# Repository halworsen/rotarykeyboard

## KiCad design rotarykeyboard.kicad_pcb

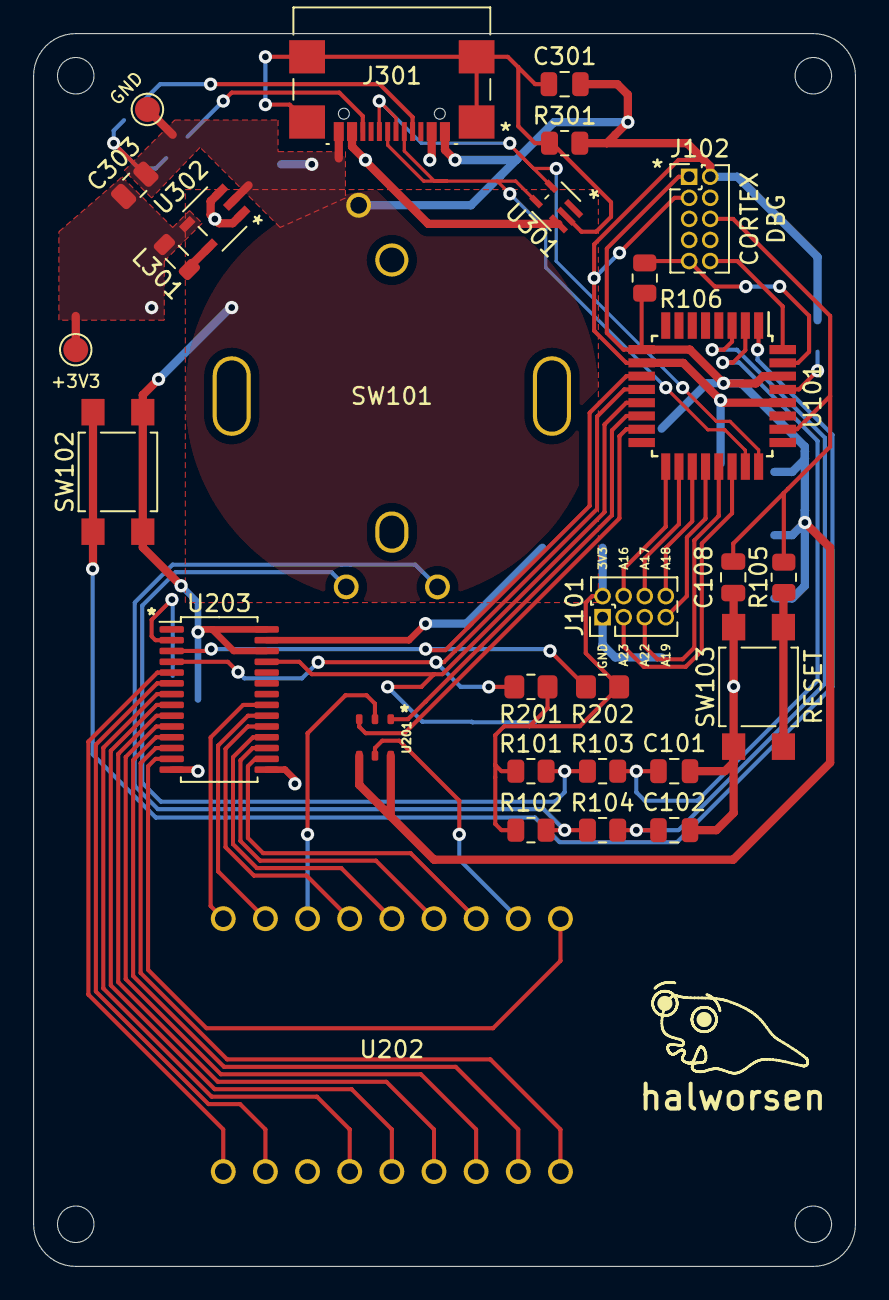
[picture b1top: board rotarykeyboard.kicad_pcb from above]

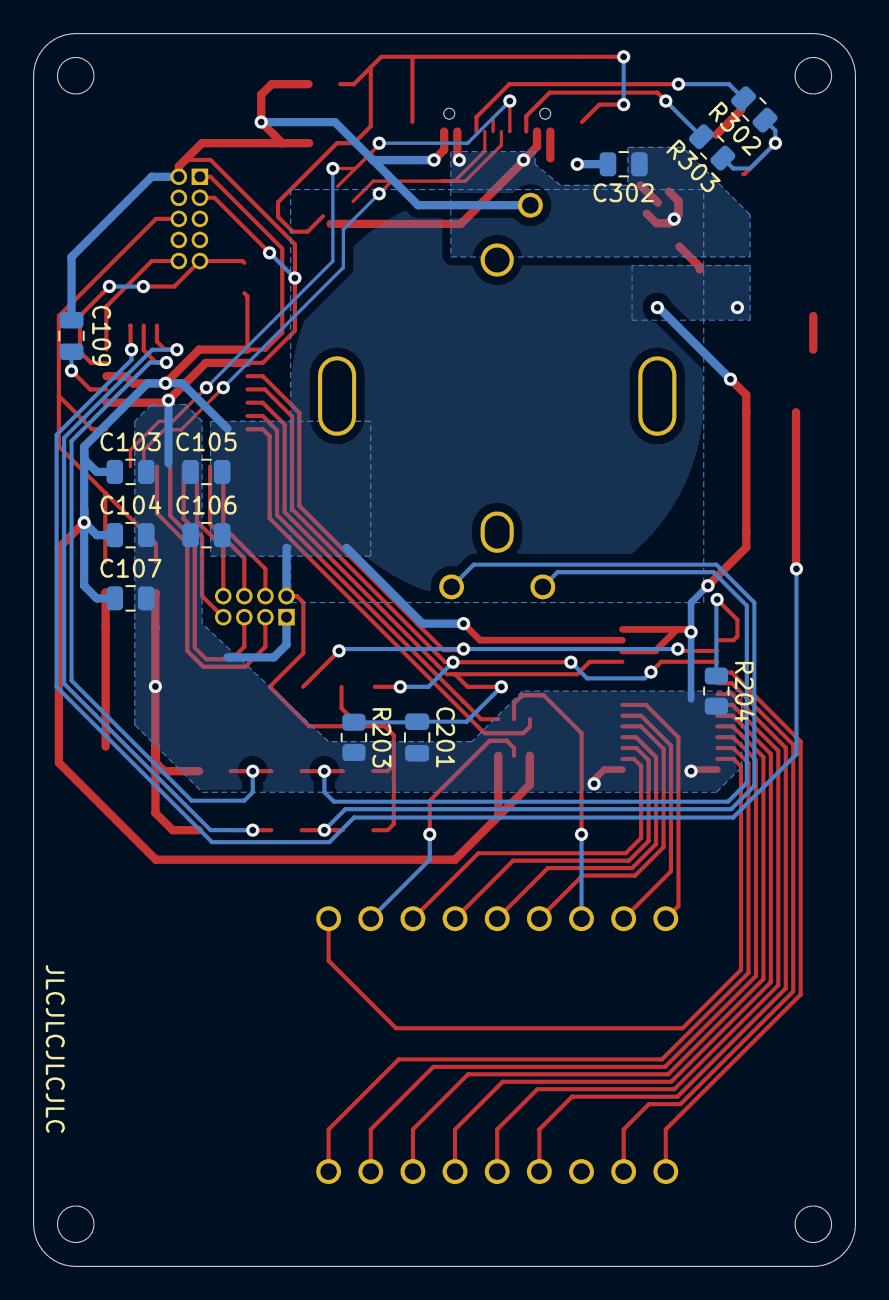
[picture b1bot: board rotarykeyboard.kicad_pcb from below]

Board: 2 copper layers, 49.5 x 74.3 mm, 41 parts (12 on the bottom side), 48 nets.

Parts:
+3V3: TestPoint; TestPoint_Pad_D1.5mm
C101, C102: 10n; C_0805_2012Metric
C103, C104, C105, C108, C201: 0.1u; C_0805_2012Metric
C106, C107, C302: 10u; C_0805_2012Metric
C109: 1u; C_0805_2012Metric
C301: 5n; C_0805_2012Metric
C303: 22u; C_0805_2012Metric
GND: TestPoint; TestPoint_Pad_D1.5mm
J101: Breakout; PinHeader_2x04_P1.27mm_Vertical
J102: Cortex Debug; PinHeader_2x05_P1.27mm_Vertical
J301: USB_C_Receptacle_USB2.0; USB4110-GF-A
L301: 10u; L_0805_2012Metric
R101, R102, R103, R104, R302, R303: 10K; R_0805_2012Metric
R105: 330; R_0805_2012Metric
R106: 1k; R_0805_2012Metric
R201, R202: 4k7; R_0805_2012Metric_Pad1.20x1.40mm_HandSolder
R203: 100k; R_0805_2012Metric
R204: 10k; R_0805_2012Metric
R301: 1M; R_0805_2012Metric
SW101: RotaryEncoder; EVQV6
SW102: KBPush; SW_SPST_TL3305A
SW103: RESET; SW_SPST_TL3305A
U101: ATSAMDA1E14B-ABT; TQFP-32_7x7mm_P0.8mm
U201: QS6K1FRATR; QS6K1FRA
U202: HDSP-A22C; LTP-3784E
U203: IS32FL3238; TSSOP-28_4.4x9.7mm_P0.65mm
U301: BZA856AVL
U302: XC9265A331MR-G

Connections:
+3V3: +3V3.1, C103.1, C104.1, C105.1, C106.1, C107.1, C303.1, J101.2, J102.1, L301.2, R101.1, R102.1, R106.2, R201.1, R202.1, U101.9 (VDDANA), U101.30 (VDDIN), U201.4 (D2), U201.6 (D1), U203.27 (VCC), U302.4 (VOUT)
+5V: C302.1, J301.A4 (VBUS), J301.A9 (VBUS), U301.3 (F), U302.1 (VIN), U302.3 (CE)
/Segment display/C1: U101.14 (PA11), U201.1 (G1)
/Segment display/C2: U101.15 (PA14), U201.3 (G2)
/Segment display/EN: C201.1, R203.1, U101.13 (PA10), U203.25 (EN)
/Segment display/SCL: R201.2, U101.12 (PA09), U203.4 (SCL)
/Segment display/SDA: R202.2, U101.11 (PA08), U203.3 (SDA)
/USB & Power/USB_D+: J301.A6 (D+), J301.B6 (D+), U101.24 (PA25), U301.5 (F)
/USB & Power/USB_D-: J301.A7 (D-), J301.B7 (D-), U101.23 (PA24), U301.4 (F)
GND: C101.2, C102.2, C103.2, C104.2, C105.2, C106.2, C107.2, C108.2, C109.2, C201.2, C301.2, C302.2, C303.2, GND.1, J101.1, J102.2, J102.3, J301.A1 (GND), J301.A12 (GND), R203.2, R204.2, R301.2, R302.1, R303.1, SW101.C, SW102.1, SW102.2, SW103.3 (K), SW103.4 (A), U101.10 (GND), U101.28 (GND), U203.14 (GND), U203.15 (GND), U203.26 (AD), U203.28 (GND), U302.2 (GND)
unnamed: C101.1, R103.2, U101.2 (PA01)
unnamed: C102.1, R104.2, U101.3 (PA02)
unnamed: C108.1, J102.6, R105.1, U101.26 (*RESET)
unnamed: C109.1, U101.29 (VDDCORE)
unnamed: C301.1, J301.S1 (SHIELD), R301.1, U301.2 (B)
unnamed: J101.3, U101.22 (PA23)
unnamed: J101.4, U101.17 (PA16)
unnamed: J101.5, U101.21 (PA22)
unnamed: J101.6, U101.18 (PA17)
unnamed: J101.7, U101.20 (PA19)
unnamed: J101.8, U101.19 (PA18)
unnamed: J102.9, R106.1, U101.31 (PA30)
unnamed: J102.10, U101.32 (PA31)
unnamed: J301.A5 (CC1), R302.2
unnamed: J301.B5 (CC2), R303.2
unnamed: L301.1, U302.5 (LX)
unnamed: R101.2, R103.1, SW101.A
unnamed: R102.2, R104.1, SW101.B
unnamed: R105.2, SW103.1, SW103.2
unnamed: R204.1, U203.2 (ISET)
unnamed: SW102.3 (K), SW102.4 (A), U101.1 (PA00)
unnamed: U201.2 (S2), U202.16 (DIG1)
unnamed: U201.5 (S1), U202.11 (DIG2)
unnamed: U202.1 (E), U203.5 (OUT1)
unnamed: U202.2 (M), U203.6 (OUT2)
unnamed: U202.4 (L), U203.7 (OUT3)
unnamed: U202.5 (K), U203.8 (OUT4)
unnamed: U202.6 (J), U203.9 (OUT5)
unnamed: U202.7 (D), U203.10 (OUT6)
unnamed: U202.8 (DP), U203.11 (OUT7)
unnamed: U202.9 (C), U203.12 (OUT8)
unnamed: U202.10 (B), U203.13 (OUT9)
unnamed: U202.12 (A), U203.16 (OUT10)
unnamed: U202.13 (N), U203.17 (OUT11)
unnamed: U202.14 (H), U203.18 (OUT12)
unnamed: U202.15 (G), U203.19 (OUT13)
unnamed: U202.17, U203.20 (OUT14)
unnamed: U202.18 (F), U203.21 (OUT15)

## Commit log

2022-01-29 all the work over christmas
2022-04-07 finish routing(?)
2022-04-08 replace out of stock components
2022-04-09 reroute new components
2022-04-09 new BOM
2022-04-09 project files cleanup
2022-04-19 påske
2022-06-08 final component changes
2022-06-08 add gerbers to gitignore
2022-06-08 production pcb
2022-07-03 bootstrap code

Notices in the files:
parts and their libraries:
Copyright 2021 Accelerated Designs. All rights reserved.
